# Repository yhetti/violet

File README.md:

# Violet
a GreatFET neighbor that is a jig for testing Gladiolus

Required KiCad dependency:

https://github.com/greatscottgadgets/gsg-kicad-lib

If you are using git, the preferred way to install gsg-kicad-lib is to use the
submodule:

```
git submodule init && git submodule update
```

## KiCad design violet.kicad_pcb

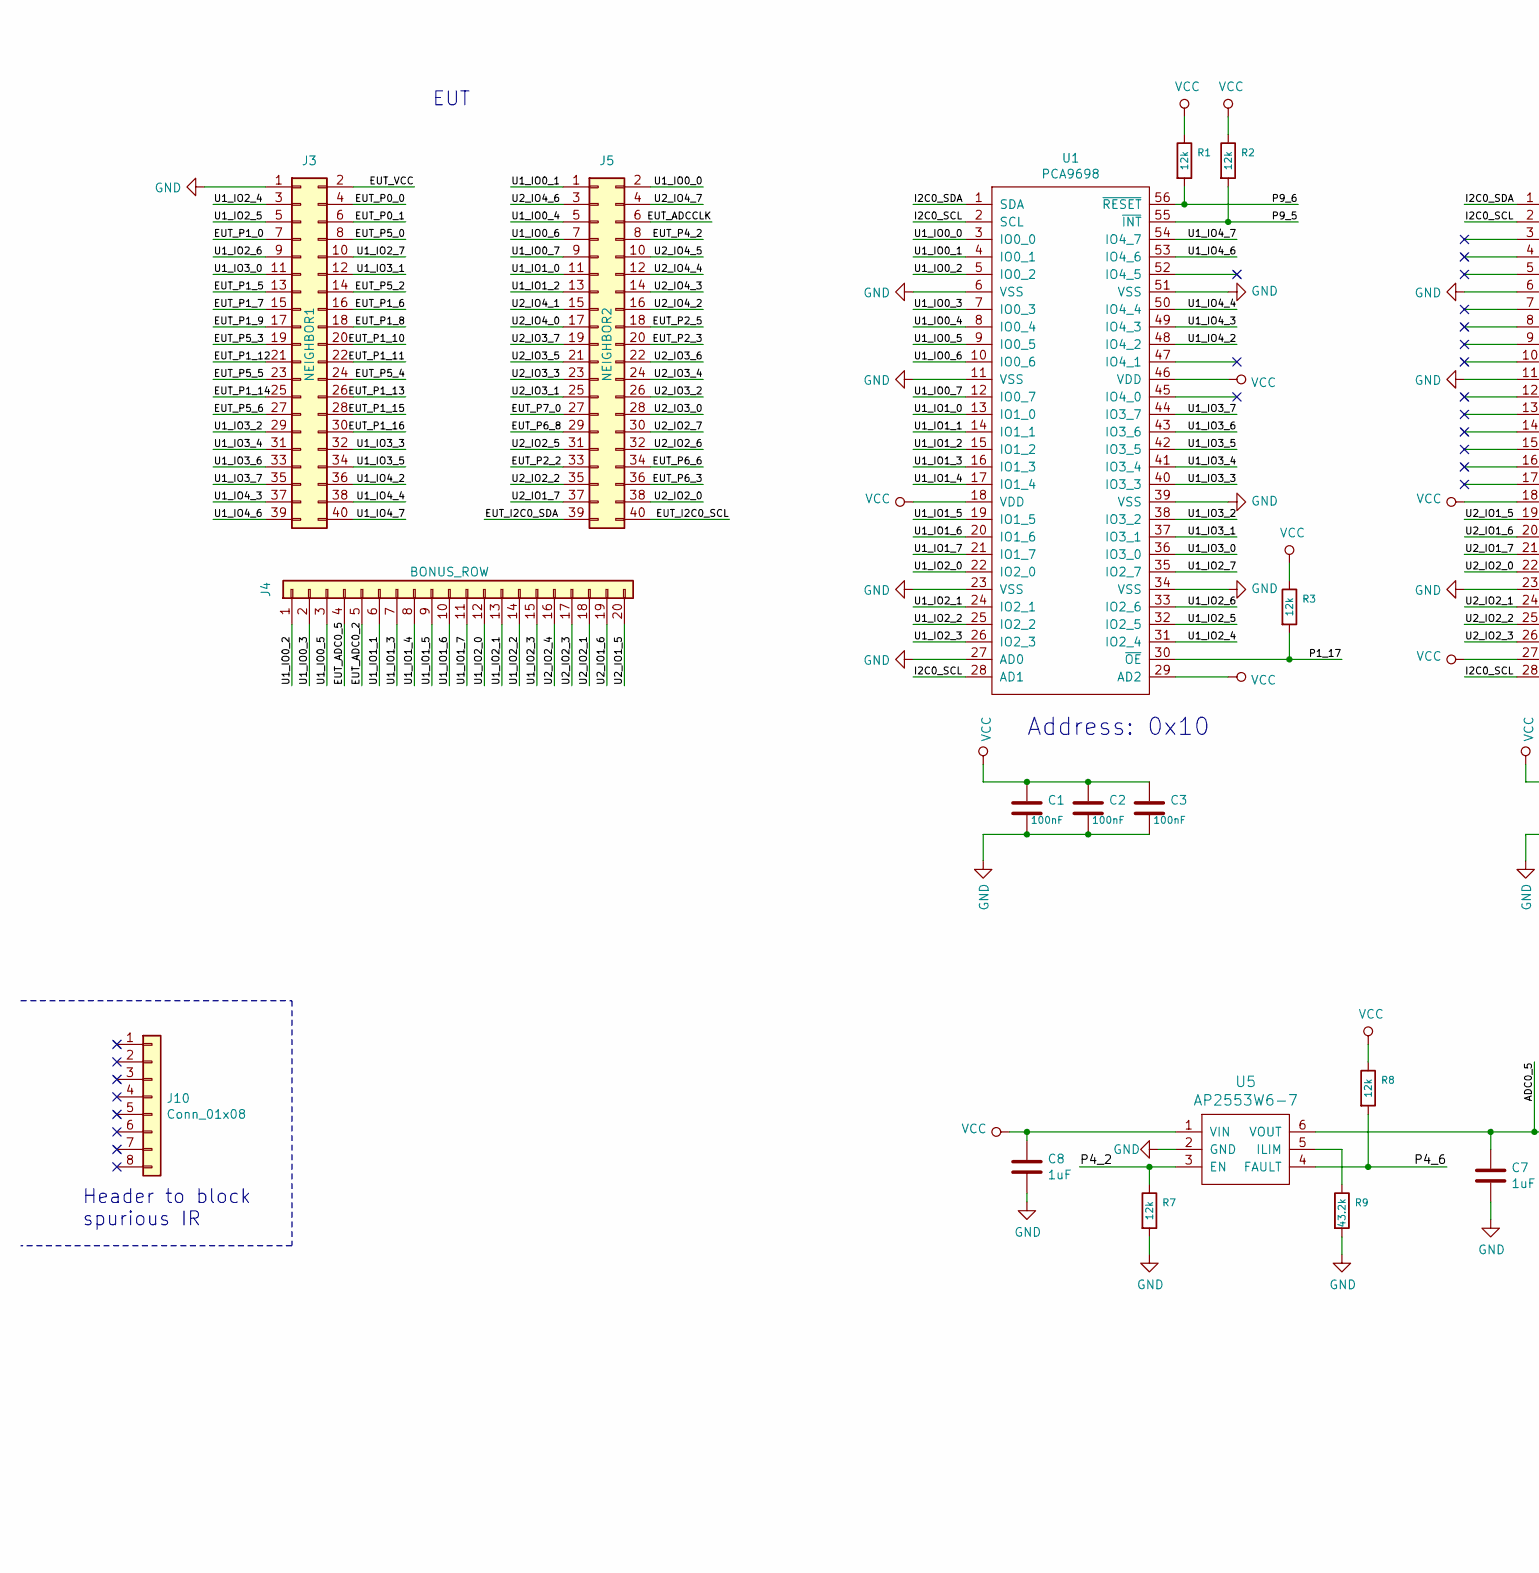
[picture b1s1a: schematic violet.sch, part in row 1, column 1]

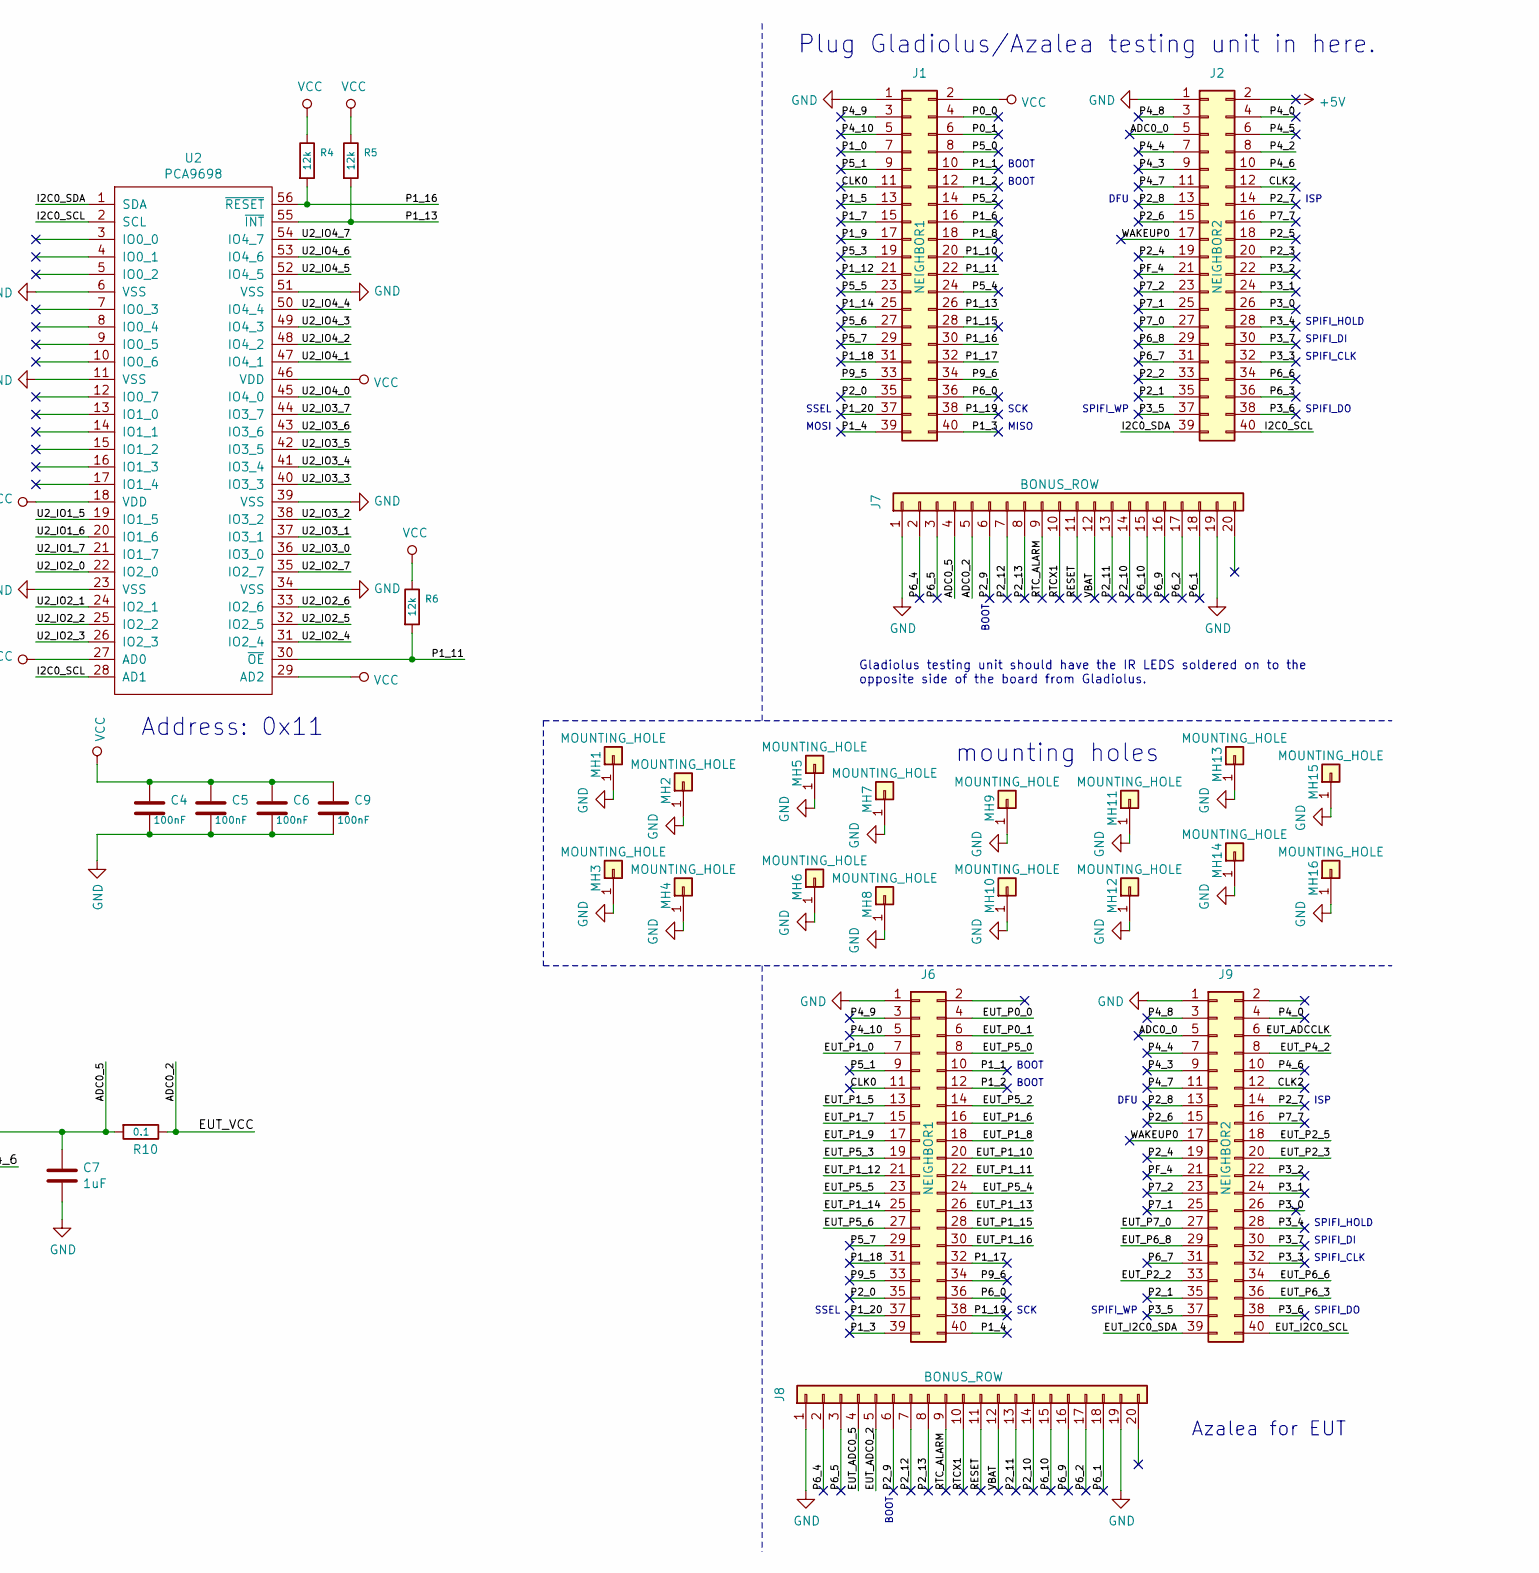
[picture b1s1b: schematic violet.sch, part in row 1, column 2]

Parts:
C1, C2, C3, C4, C5, C6, C9: 100nF; 0603; Part Number C0603C104M4RACTU
C7, C8: 1uF; 0603; Part Number CL10A105KP8NNNC
J1, J3, J6: NEIGHBOR1; HEADER-2x20; Part Number PH2-20-UA
J2, J5, J9: NEIGHBOR2; HEADER-2x20; Part Number PH2-20-UA
J4, J7, J8: BONUS_ROW; HEADER-1x20; Part Number SSQ-120-23-G-S
J10: Conn_01x08; HEADER-1x8; Part Number SSQ-108-01-G-S
MH1, MH2, MH3, MH4, MH5, MH6, MH7, MH8, MH9, MH10, MH11, MH12, MH13, MH14, MH15, MH16: MOUNTING_HOLE; HOLE126MIL-COPPER
R1, R2, R3, R4, R5, R6, R7, R8: 12k; 0603; Part Number RMCF0603FT12K0
R9: 43.2k; 0603; Part Number RC0603FR-0743K2L
R10: 0.1; 0603; Part Number ERJ-3RSFR10V
U1, U2: PCA9698; TSSOP56; Part Number PCA9698DGG,512
U5: AP2553W6-7; SOT457

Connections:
+5V: J2.2
/ADC0_0: J2.5, J9.5
/ADC0_2: J3.2, J7.5, R10.1
/ADC0_5: C7.1, J7.4, R10.2, U5.6 (VOUT)
/CLK0: J1.11, J6.11
/CLK2: J2.12, J9.12
/EUT_ADC0_2: J4.5, J8.5
/EUT_ADC0_5: J4.4, J8.4
/EUT_ADCCLK: J5.6, J9.6
/EUT_I2C0_SCL: J5.40, J9.40
/EUT_I2C0_SDA: J5.39, J9.39
/EUT_P0_0: J3.4, J6.4
/EUT_P0_1: J3.6, J6.6
/EUT_P1_0: J3.7, J6.7
/EUT_P1_5: J3.13, J6.13
/EUT_P1_6: J3.16, J6.16
/EUT_P1_7: J3.15, J6.15
/EUT_P1_8: J3.18, J6.18
/EUT_P1_9: J3.17, J6.17
/EUT_P1_10: J3.20, J6.20
/EUT_P1_11: J3.22, J6.22
/EUT_P1_12: J3.21, J6.21
/EUT_P1_13: J3.26, J6.26
/EUT_P1_14: J3.25, J6.25
/EUT_P1_15: J3.28, J6.28
/EUT_P1_16: J3.30, J6.30
/EUT_P2_2: J5.33, J9.33
/EUT_P2_3: J5.20, J9.20
/EUT_P2_5: J5.18, J9.18
/EUT_P4_2: J5.8, J9.8
/EUT_P5_0: J3.8, J6.8
/EUT_P5_2: J3.14, J6.14
/EUT_P5_3: J3.19, J6.19
/EUT_P5_4: J3.24, J6.24
/EUT_P5_5: J3.23, J6.23
/EUT_P5_6: J3.27, J6.27
/EUT_P6_3: J5.36, J9.36
/EUT_P6_6: J5.34, J9.34
/EUT_P6_8: J5.29, J9.29
/EUT_P7_0: J5.27, J9.27
/I2C0_SCL: J2.40, U1.2 (SCL), U1.28 (AD1), U2.2 (SCL), U2.28 (AD1)
/I2C0_SDA: J2.39, U1.1 (SDA), U2.1 (SDA)
/P0_0: J1.4
/P0_1: J1.6
/P1_0: J1.7
/P1_1: J1.10, J6.10
/P1_2: J1.12, J6.12
/P1_3: J1.40, J6.39
/P1_4: J1.39, J6.40
/P1_5: J1.13
/P1_6: J1.16
/P1_7: J1.15
/P1_8: J1.18
/P1_9: J1.17
/P1_10: J1.20
/P1_11: J1.22, R6.2, U2.30 (~OE~)
/P1_12: J1.21
/P1_13: J1.26, R5.2, U2.55 (~INT~)
/P1_14: J1.25
/P1_15: J1.28
/P1_16: J1.30, R4.2, U2.56 (~RESET~)
/P1_17: J1.32, J6.32, R3.2, U1.30 (~OE~)
/P1_18: J1.31, J6.31
/P1_19: J1.38, J6.38
/P1_20: J1.37, J6.37
/P2_0: J1.35, J6.35
/P2_1: J2.35, J9.35
/P2_2: J2.33
/P2_3: J2.20
/P2_4: J2.19, J9.19
/P2_5: J2.18
/P2_6: J2.15, J9.15
/P2_7: J2.14, J9.14
/P2_8: J2.13, J9.13
/P2_9: J7.6, J8.6
/P2_10: J7.14, J8.14
/P2_11: J7.13, J8.13
/P2_12: J7.7, J8.7
/P2_13: J7.8, J8.8
/P3_0: J2.26, J9.26
/P3_1: J2.24, J9.24
/P3_2: J2.22, J9.22
/P3_3: J2.32, J9.32
/P3_4: J2.28, J9.28
/P3_5: J2.37, J9.37
/P3_6: J2.38, J9.38
/P3_7: J2.30, J9.30
/P4_0: J2.4, J9.4
/P4_2: J2.8, R7.1, U5.3 (EN)
/P4_3: J2.9, J9.9
/P4_4: J2.7, J9.7
/P4_5: J2.6
/P4_6: J2.10, J9.10, R8.2, U5.4 (FAULT)
/P4_7: J2.11, J9.11
/P4_8: J2.3, J9.3
/P4_9: J1.3, J6.3
/P4_10: J1.5, J6.5
/P5_0: J1.8
/P5_1: J1.9, J6.9
/P5_2: J1.14
/P5_3: J1.19
/P5_4: J1.24
/P5_5: J1.23
/P5_6: J1.27
/P5_7: J1.29, J6.29
/P6_0: J1.36, J6.36
/P6_1: J7.18, J8.18
/P6_2: J7.17, J8.17
/P6_3: J2.36
/P6_4: J7.2, J8.2
/P6_5: J7.3, J8.3
/P6_6: J2.34
/P6_7: J2.31, J9.31
/P6_8: J2.29
/P6_9: J7.16, J8.16
/P6_10: J7.15, J8.15
/P7_0: J2.27
/P7_1: J2.25, J9.25
/P7_2: J2.23, J9.23
/P7_7: J2.16, J9.16
/P9_5: J1.33, J6.33, R2.2, U1.55 (~INT~)
/P9_6: J1.34, J6.34, R1.2, U1.56 (~RESET~)
/PF_4: J2.21, J9.21
/RESET: J7.11, J8.11
/RTCX1: J7.10, J8.10
/RTC_ALARM: J7.9, J8.9
/U1_IO0_0: J5.2, U1.3 (IO0_0)
/U1_IO0_1: J5.1, U1.4 (IO0_1)
/U1_IO0_2: J4.1, U1.5 (IO0_2)
/U1_IO0_3: J4.2, U1.7 (IO0_3)
/U1_IO0_4: J5.5, U1.8 (IO0_4)
/U1_IO0_5: J4.3, U1.9 (IO0_5)
/U1_IO0_6: J5.7, U1.10 (IO0_6)
/U1_IO0_7: J5.9, U1.12 (IO0_7)
/U1_IO1_0: J5.11, U1.13 (IO1_0)
/U1_IO1_1: J4.6, U1.14 (IO1_1)
/U1_IO1_2: J5.13, U1.15 (IO1_2)
/U1_IO1_3: J4.7, U1.16 (IO1_3)
/U1_IO1_4: J4.8, U1.17 (IO1_4)
/U1_IO1_5: J4.9, U1.19 (IO1_5)
/U1_IO1_6: J4.10, U1.20 (IO1_6)
/U1_IO1_7: J4.11, U1.21 (IO1_7)
/U1_IO2_0: J4.12, U1.22 (IO2_0)
/U1_IO2_1: J4.13, U1.24 (IO2_1)
/U1_IO2_2: J4.14, U1.25 (IO2_2)
/U1_IO2_3: J4.15, U1.26 (IO2_3)
/U1_IO2_4: J3.3, U1.31 (IO2_4)
/U1_IO2_5: J3.5, U1.32 (IO2_5)
/U1_IO2_6: J3.9, U1.33 (IO2_6)
/U1_IO2_7: J3.10, U1.35 (IO2_7)
/U1_IO3_0: J3.11, U1.36 (IO3_0)
/U1_IO3_1: J3.12, U1.37 (IO3_1)
/U1_IO3_2: J3.29, U1.38 (IO3_2)
/U1_IO3_3: J3.32, U1.40 (IO3_3)
/U1_IO3_4: J3.31, U1.41 (IO3_4)
/U1_IO3_5: J3.34, U1.42 (IO3_5)
/U1_IO3_6: J3.33, U1.43 (IO3_6)
/U1_IO3_7: J3.35, U1.44 (IO3_7)
/U1_IO4_2: J3.36, U1.48 (IO4_2)
/U1_IO4_3: J3.37, U1.49 (IO4_3)
/U1_IO4_4: J3.38, U1.50 (IO4_4)
/U1_IO4_6: J3.39, U1.53 (IO4_6)
/U1_IO4_7: J3.40, U1.54 (IO4_7)
/U2_IO1_5: J4.20, U2.19 (IO1_5)
/U2_IO1_6: J4.19, U2.20 (IO1_6)
/U2_IO1_7: J5.37, U2.21 (IO1_7)
/U2_IO2_0: J5.38, U2.22 (IO2_0)
/U2_IO2_1: J4.18, U2.24 (IO2_1)
/U2_IO2_2: J5.35, U2.25 (IO2_2)
/U2_IO2_3: J4.17, U2.26 (IO2_3)
/U2_IO2_4: J4.16, U2.31 (IO2_4)
/U2_IO2_5: J5.31, U2.32 (IO2_5)
/U2_IO2_6: J5.32, U2.33 (IO2_6)
/U2_IO2_7: J5.30, U2.35 (IO2_7)
/U2_IO3_0: J5.28, U2.36 (IO3_0)
/U2_IO3_1: J5.25, U2.37 (IO3_1)
/U2_IO3_2: J5.26, U2.38 (IO3_2)
/U2_IO3_3: J5.23, U2.40 (IO3_3)
/U2_IO3_4: J5.24, U2.41 (IO3_4)
/U2_IO3_5: J5.21, U2.42 (IO3_5)
/U2_IO3_6: J5.22, U2.43 (IO3_6)
/U2_IO3_7: J5.19, U2.44 (IO3_7)
/U2_IO4_0: J5.17, U2.45 (IO4_0)
/U2_IO4_1: J5.15, U2.47 (IO4_1)
/U2_IO4_2: J5.16, U2.48 (IO4_2)
/U2_IO4_3: J5.14, U2.49 (IO4_3)
/U2_IO4_4: J5.12, U2.50 (IO4_4)
/U2_IO4_5: J5.10, U2.52 (IO4_5)
/U2_IO4_6: J5.3, U2.53 (IO4_6)
/U2_IO4_7: J5.4, U2.54 (IO4_7)
/VBAT: J7.12, J8.12
/WAKEUP0: J2.17, J9.17
GND: C1.2, C2.2, C3.2, C4.2, C5.2, C6.2, C7.2, C8.2, C9.2, J1.1, J2.1, J3.1, J6.1, J7.1, J7.19, J8.1, J8.19, J9.1, MH1.1, MH2.1, MH3.1, MH4.1, MH5.1, MH6.1, MH7.1, MH8.1, MH9.1, MH10.1, MH11.1, MH12.1, MH13.1, MH14.1, MH15.1, MH16.1, R7.2, R9.2, U1.6 (VSS), U1.11 (VSS), U1.23 (VSS), U1.27 (AD0), U1.34 (VSS), U1.39 (VSS), U1.51 (VSS), U2.6 (VSS), U2.11 (VSS), U2.23 (VSS), U2.34 (VSS), U2.39 (VSS), U2.51 (VSS), U5.2 (GND)
unnamed: R9.1, U5.5 (ILIM)
VCC: C1.1, C2.1, C3.1, C4.1, C5.1, C6.1, C8.1, C9.1, J1.2, R1.1, R2.1, R3.1, R4.1, R5.1, R6.1, R8.1, U1.18 (VDD), U1.29 (AD2), U1.46 (VDD), U2.18 (VDD), U2.27 (AD0), U2.29 (AD2), U2.46 (VDD), U5.1 (VIN)

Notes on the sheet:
MISO
MOSI
SCK
SSEL
ISP
DFU
BOOT
SPIFI_CLK
SPIFI_HOLD
SPIFI_WP
SPIFI_DO
SPIFI_DI
Gladiolus testing unit should have the IR LEDS soldered on to the opposite side of the board from Gladiolus.
Plug Gladiolus/Azalea testing unit in here.
mounting holes
EUT
Azalea for EUT
Address: 0x10
Address: 0x11
Header to block spurious IR

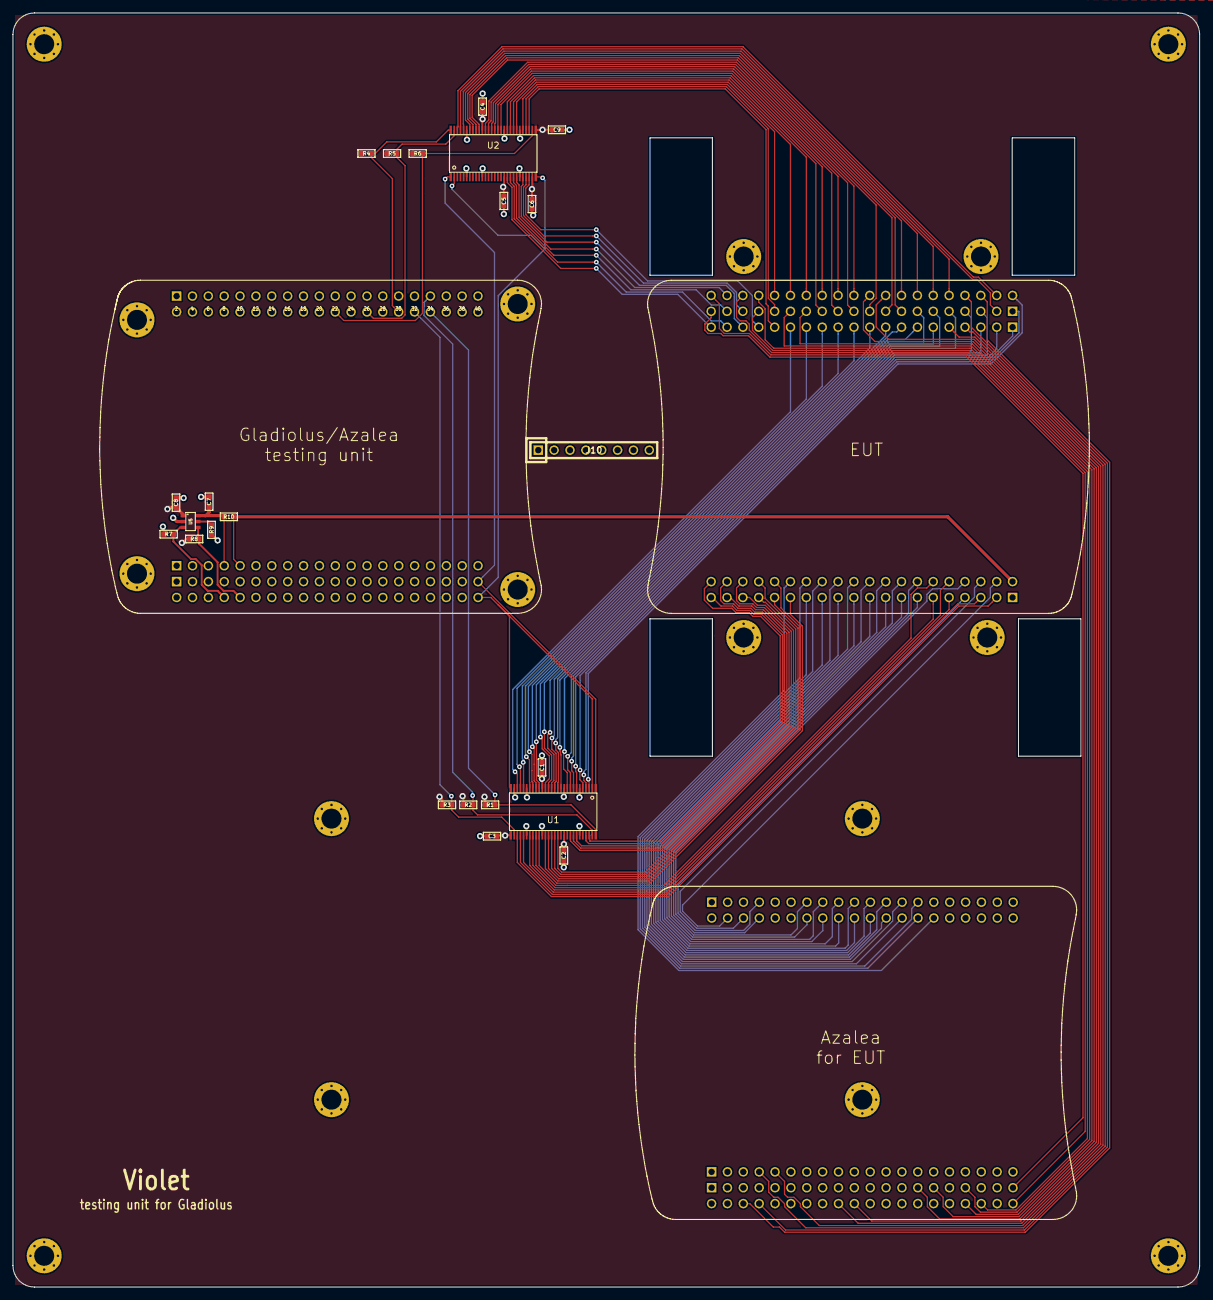
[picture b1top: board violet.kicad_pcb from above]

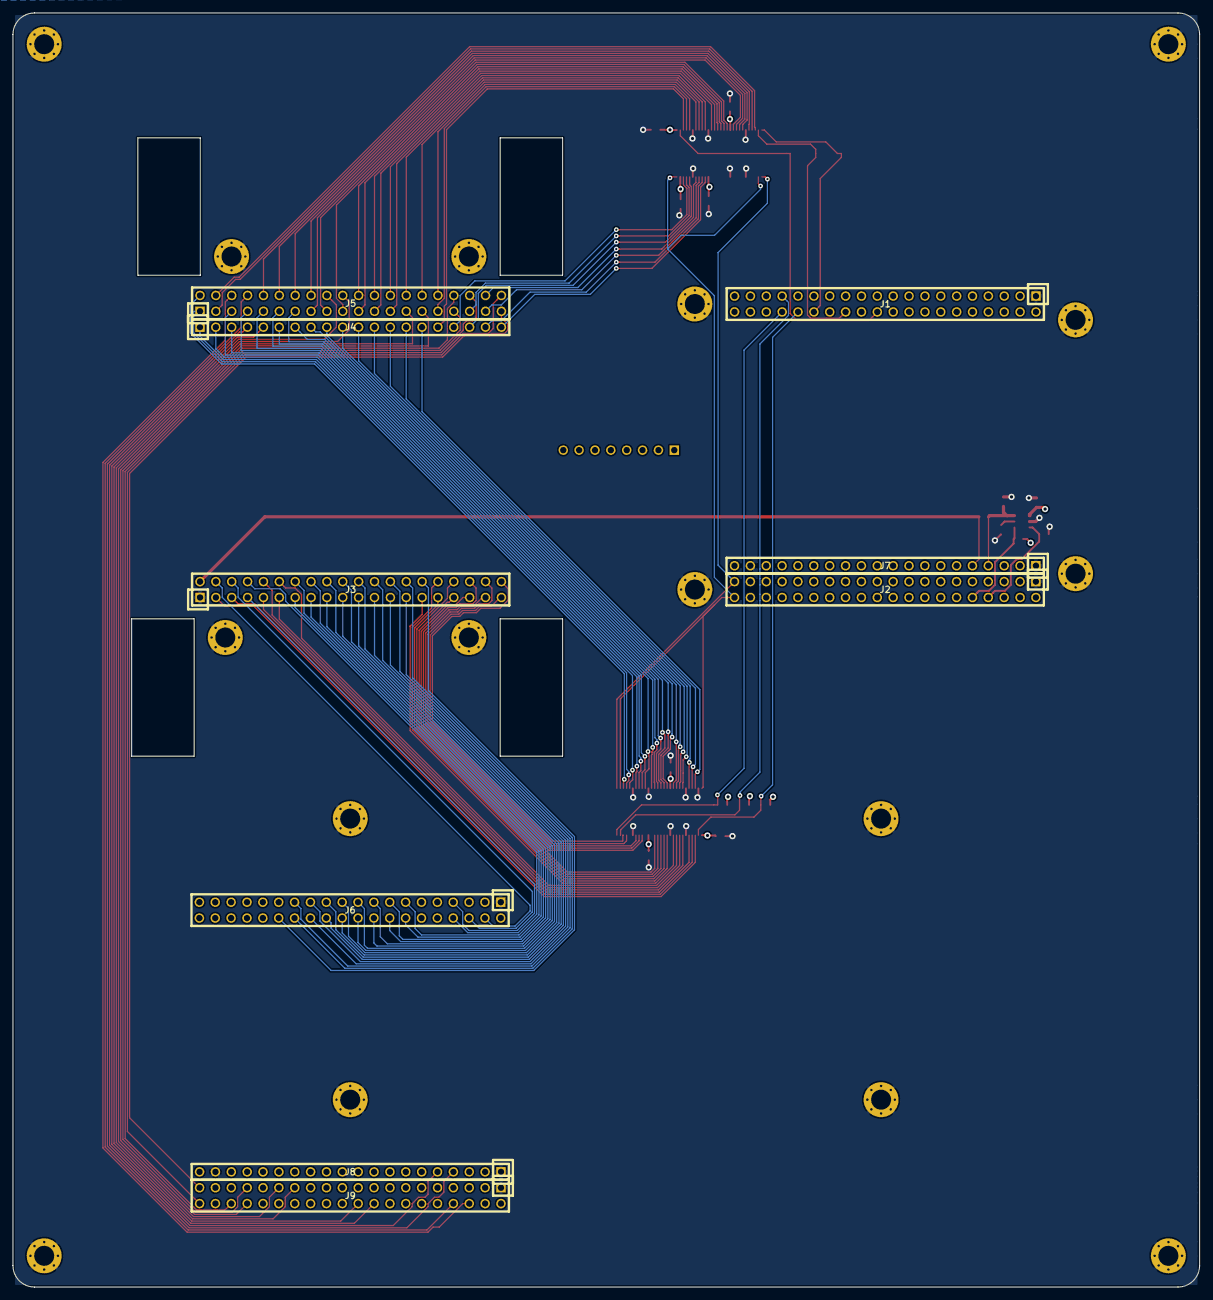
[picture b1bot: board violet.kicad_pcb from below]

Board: 2 copper layers, 190.0 x 204.0 mm, 48 parts (9 on the bottom side), 168 nets.

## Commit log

2020-02-29 Initial commit; Create kicad files; Add gsg-kicad-lib submodule
2020-09-24 set up initial configuration of headers
2020-09-24 Add header set for EUT Azalea; wire RX/TX signals between EUT and EUT Azalea
2021-01-07 Add labels to I/O expanders and headers
2021-01-08 Add more labels; fix label nomenclature
2021-01-09 Add more labels; add another I/O expander
2021-01-12 Add remaining labels; configure third I/O expander; add decoupling caps
2021-01-12 Add parts and footprints
2021-01-12 Annotate schematic symbols
2021-01-14 Remove U3 & U4; re-label signals; set up U5; fix U1 &U2 I2C addresses; fix minor errors
2021-01-15 Add remaining footprints
2021-01-15 generate net list
2021-01-15 Place and orient headers on pcb
2021-01-16 Layout power supply for EUT
2021-01-19 Wire J6 to J3
2021-01-19 Add more mounting holes
2021-01-19 Fix mounting hole footprints
2021-01-20 Wire J8/9 to J4/5; place new mounting holes; begin wiring U1
2021-01-20 Re-map I/O expanders for easier routing
2021-01-21 Route most of U1
2021-01-21 Complete routing of PCB; update routing in schematic for ease of routing on PCB
2021-01-22 Update LICENSE to CERN-OHL-P v2
